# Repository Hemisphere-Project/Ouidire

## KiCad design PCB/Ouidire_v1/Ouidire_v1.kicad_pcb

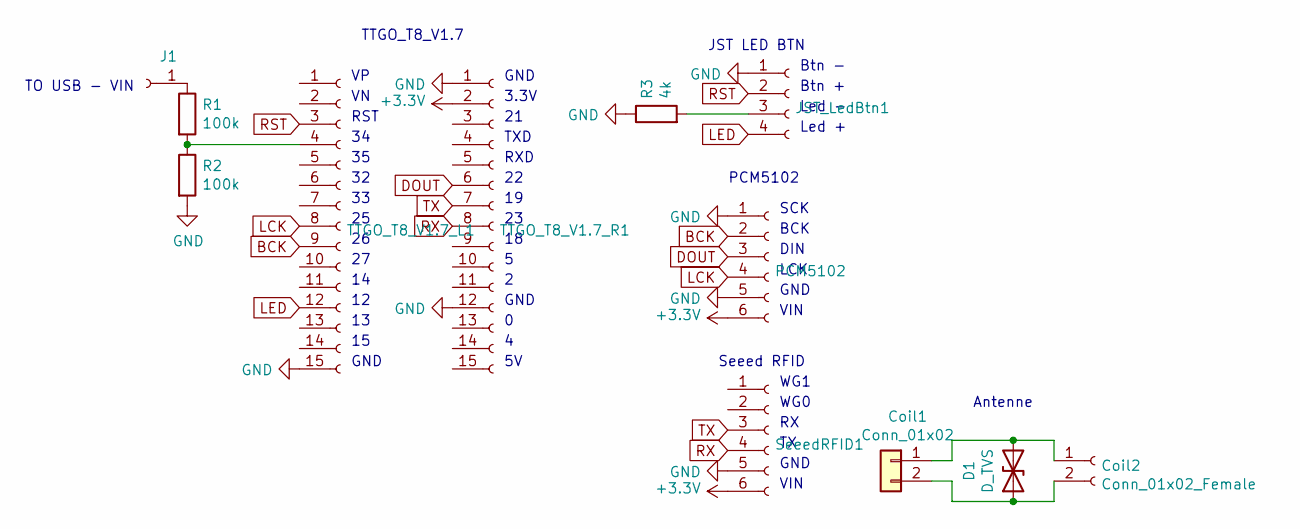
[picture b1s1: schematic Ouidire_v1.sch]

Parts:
Coil1: Conn_01x02; PinSocket_1x02_P2.54mm_Vertical
Coil2: Conn_01x02_Female; PinSocket_1x02_P2.54mm_Vertical
D1: D_TVS; D_DO-35_SOD27_P7.62mm_Horizontal
J1: Conn_01x01_Female; PinSocket_1x01_P2.54mm_Vertical
JST_LedBtn1: Conn_01x04_Female; PinSocket_1x04_P2.54mm_Vertical
PCM5102: Conn_01x06_Female; PinSocket_1x06_P2.54mm_Vertical
R1, R2: 100k; R_1206_3216Metric_Pad1.42x1.75mm_HandSolder
R3: 4k; R_1206_3216Metric_Pad1.42x1.75mm_HandSolder
SeeedRFID1: Conn_01x06_Female; PinSocket_1x06_P2.54mm_Vertical
TTGO_T8_V1.7_L1, TTGO_T8_V1.7_R1: Conn_01x15_Female; PinSocket_1x15_P2.54mm_Vertical

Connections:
+3V3: PCM5102.6, SeeedRFID1.6, TTGO_T8_V1.7_R1.2
BCK: PCM5102.2, TTGO_T8_V1.7_L1.9
DOUT: PCM5102.3, TTGO_T8_V1.7_R1.6
GND: JST_LedBtn1.1, PCM5102.1, PCM5102.5, R2.2, R3.1, SeeedRFID1.5, TTGO_T8_V1.7_L1.15, TTGO_T8_V1.7_R1.1, TTGO_T8_V1.7_R1.12
LCK: PCM5102.4, TTGO_T8_V1.7_L1.8
LED: JST_LedBtn1.4, TTGO_T8_V1.7_L1.12
unnamed: Coil1.1, Coil2.1, D1.2 (A2)
unnamed: Coil1.2, Coil2.2, D1.1 (A1)
unnamed 8: J1.1, R1.1; also elsewhere on the board
unnamed: JST_LedBtn1.3, R3.2
unnamed: R1.2, R2.1, TTGO_T8_V1.7_L1.4
RST: JST_LedBtn1.2, TTGO_T8_V1.7_L1.3
RX: SeeedRFID1.4, TTGO_T8_V1.7_R1.8
TX: SeeedRFID1.3, TTGO_T8_V1.7_R1.7

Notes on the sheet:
Antenne
TTGO_T8_V1.7
PCM5102
Seeed RFID
TO USB - VIN
JST LED BTN
Btn -
Btn +
Led -
Led +
RST
GND
3.3V
TXD
RXD
SCK
BCK
DIN
LCK
VIN
WG1
WG0

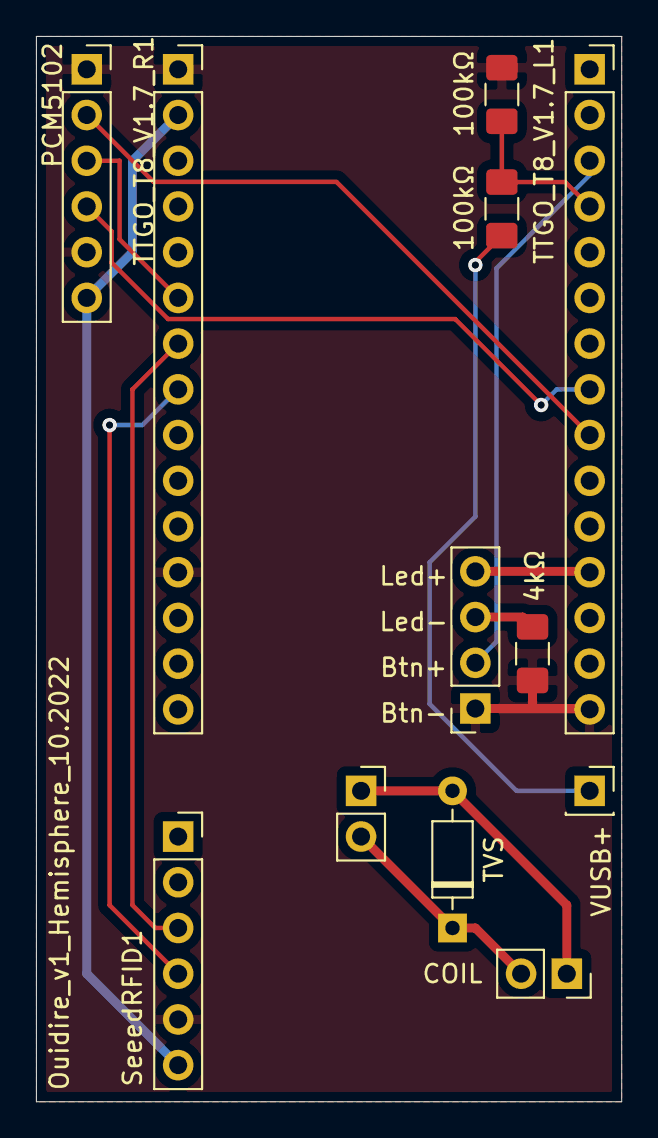
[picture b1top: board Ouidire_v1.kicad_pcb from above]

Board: 2 copper layers, 32.5 x 59.2 mm, 12 parts (0 on the bottom side), 14 nets.

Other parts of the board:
VUSB+: Conn_01x01_Female; PinSocket_1x01_P2.54mm_Vertical

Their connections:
unnamed 8: VUSB+.1; also elsewhere on the board

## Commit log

2022-07-20 start
2022-09-16 battery monitor
2022-09-23 boitier forme ok
2022-09-27 casing proto done
2022-09-30 PCB Netlist & placement ok
2022-10-03 pcb v1 ok
2022-10-04 Blink states ok
2022-10-20 Play hello on start & set volume
2022-11-03 dock
2023-02-27 boitier v3
2023-03-29 medias 20230328
